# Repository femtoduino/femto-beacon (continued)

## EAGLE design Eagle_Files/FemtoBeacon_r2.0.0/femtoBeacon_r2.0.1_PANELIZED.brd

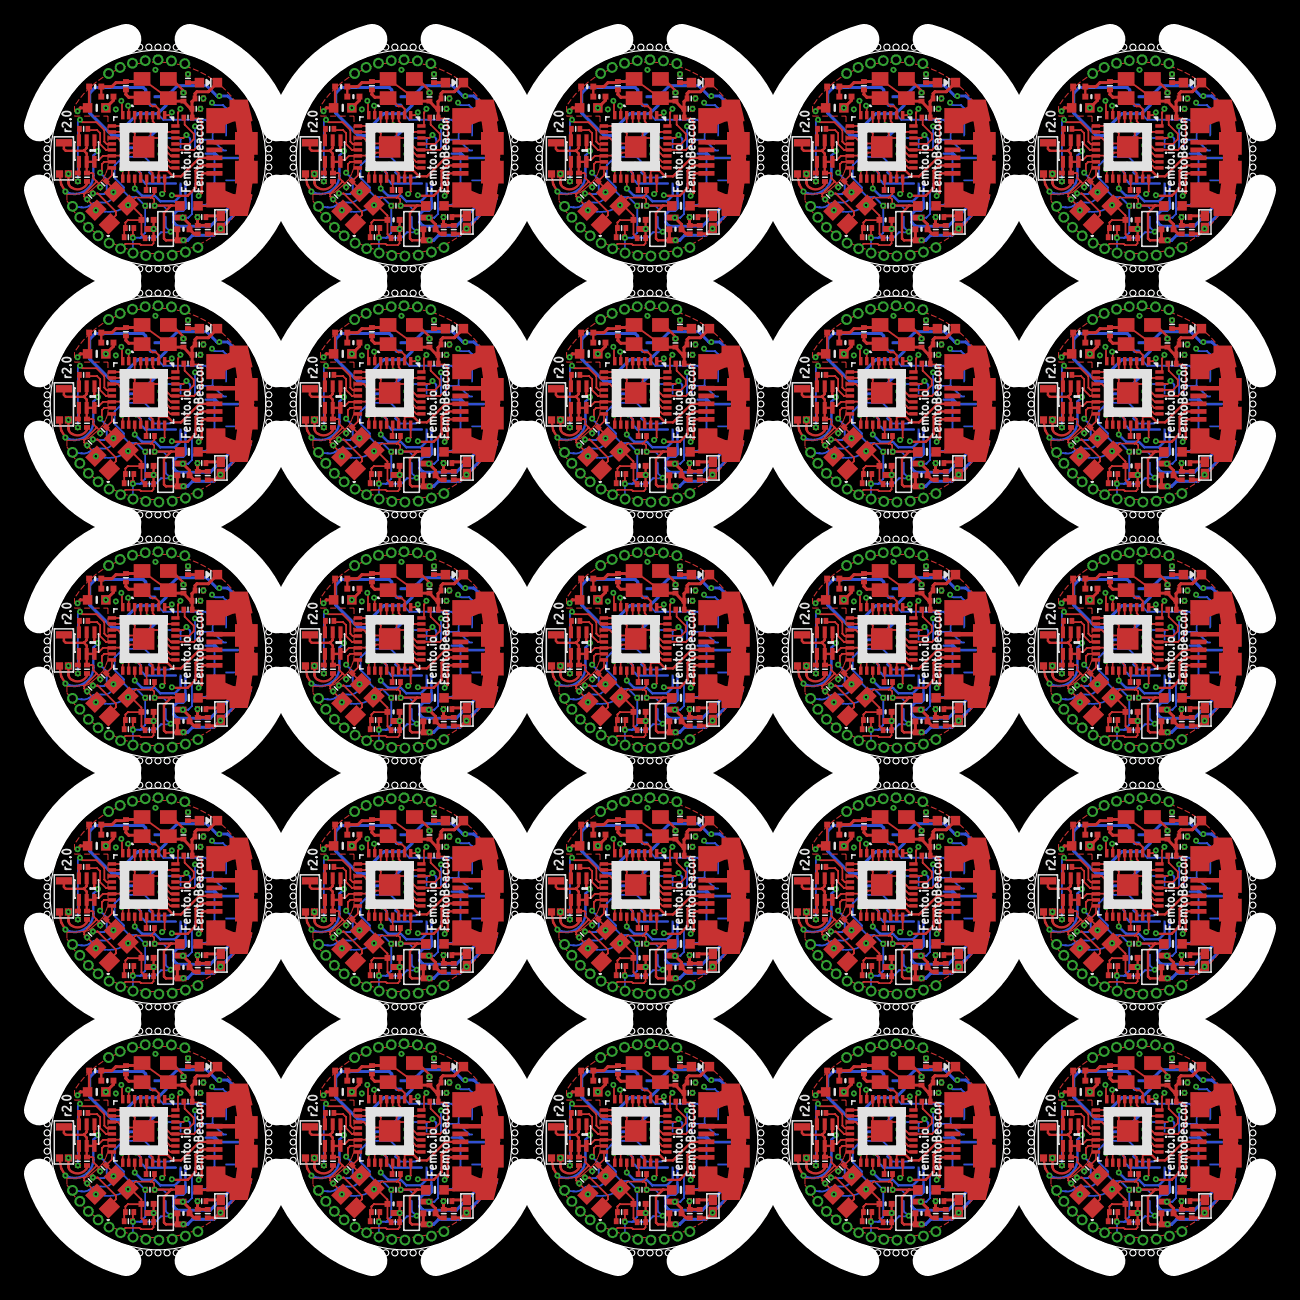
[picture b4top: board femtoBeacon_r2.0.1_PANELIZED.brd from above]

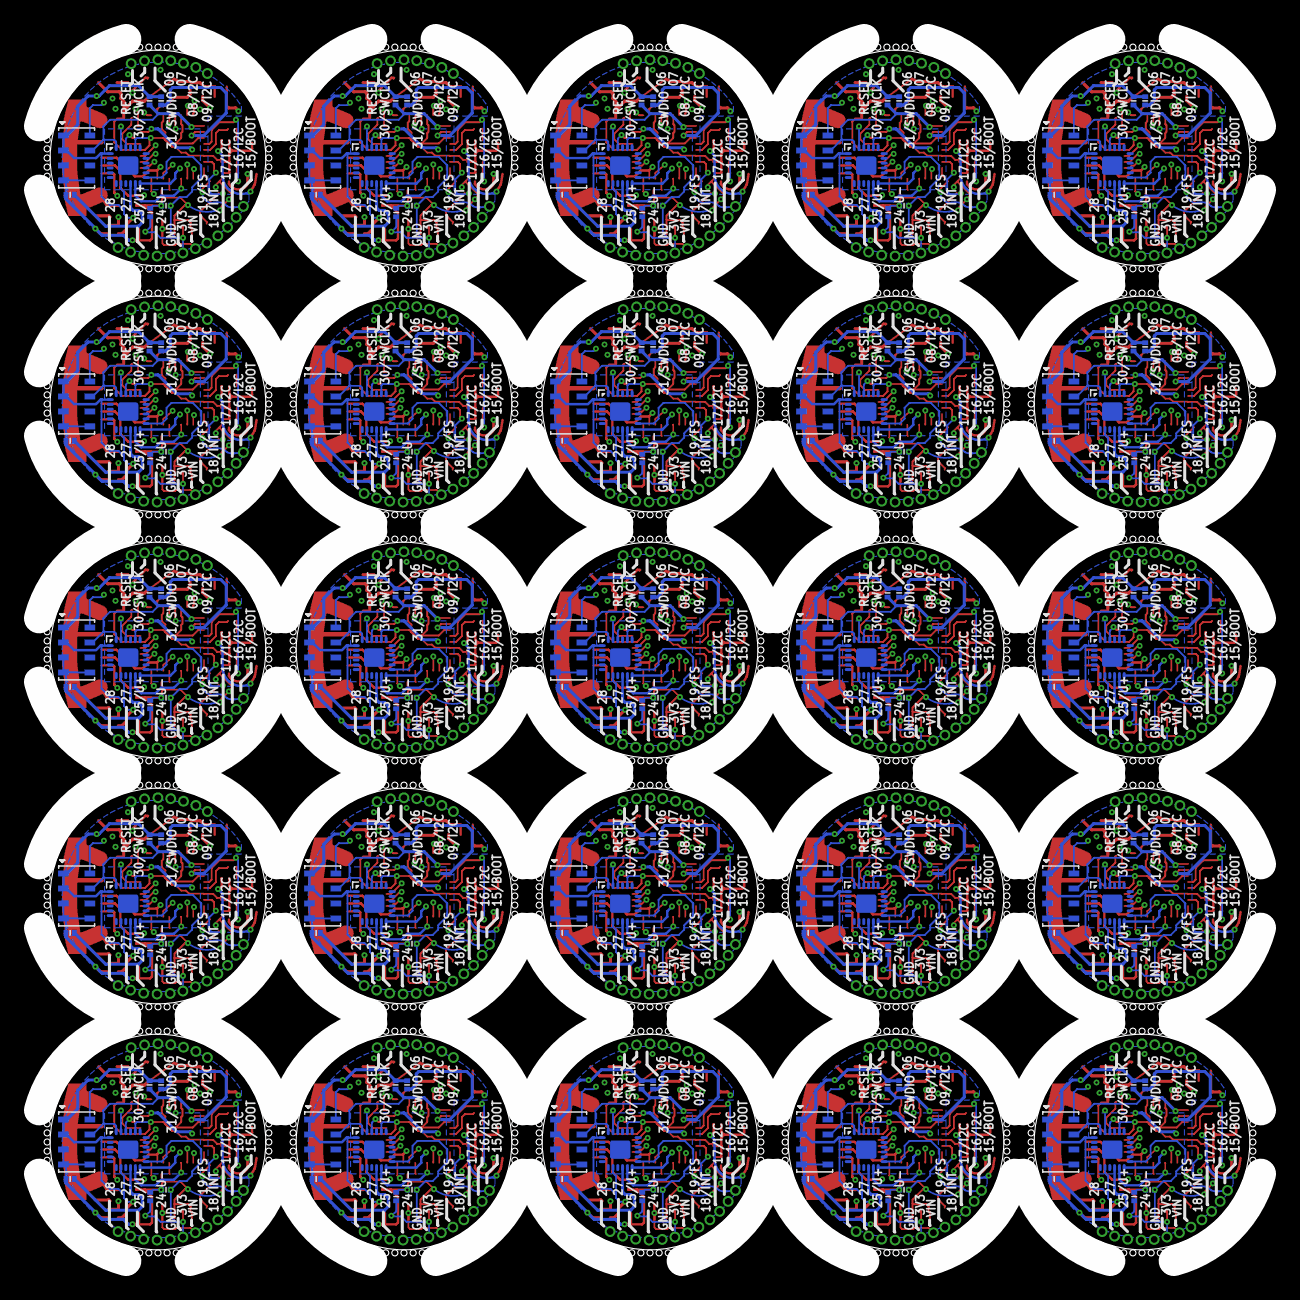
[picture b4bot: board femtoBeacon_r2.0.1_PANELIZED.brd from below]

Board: 4 copper layers, 102.0 x 102.0 mm, 1500 parts (175 on the bottom side), 900 nets.

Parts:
ANT, ANT1, ANT2, ANT3, ANT4, ANT5, ANT6, ANT7, ANT8, ANT9, ANT10, ANT11, ANT12, ANT13, ANT14, ANT15, ANT16, ANT17, ANT18, ANT19, ANT20, ANT21, ANT22, ANT23, ANT24: PULSE_ANT_2.4GHZ; ANT_BAR
BAL, BAL1, BAL2, BAL3, BAL4, BAL5, BAL6, BAL7, BAL8, BAL9, BAL10, BAL11, BAL12, BAL13, BAL14, BAL15, BAL16, BAL17, BAL18, BAL19, BAL20, BAL21, BAL22, BAL23, BAL24: JOHANSON_2450BM15A0015E; 0805_BALUN
BARO, BARO1, BARO2, BARO3, BARO4, BARO5, BARO6, BARO7, BARO8, BARO9, BARO10, BARO11, BARO12, BARO13, BARO14, BARO15, BARO16, BARO17, BARO18, BARO19, BARO20, BARO21, BARO22, BARO23, BARO24: MS5611-01BA03
BTN, BTN1, BTN2, BTN3, BTN4, BTN5, BTN6, BTN7, BTN8, BTN9, BTN10, BTN11, BTN12, BTN13, BTN14, BTN15, BTN16, BTN17, BTN18, BTN19, BTN20, BTN21, BTN22, BTN23, BTN24: DNP; SPST_SMD
C1, C2, C8, C9, C10, C16, C17, C18, C19, C25, C26, C27, C28, C29, C30, C32, C33, C36, C45, C46, C47, C48, C52, C53, C54, C55, C56, C59, C68, C69, C70, C71, C75, C76, C77, C78, C79, C82, C91, C92, C93, C94, C98, C99, C100, C101, C102, C105, C114, C115, C116, C117, C121, C122, C123, C124, C125, C128, C137, C138, C139, C140, C144, C145, C146, C147, C148, C151, C160, C161, C162, C163, C167, C168, C169, C170, C171, C174, C183, C184, C185, C186, C190, C191, C192, C193, C194, C197, C206, C207, C208, C209, C213, C214, C215, C216, C217, C220, C229, C230, C231, C232, C236, C237, C238, C239, C240, C243, C252, C253, C254, C255, C259, C260, C261, C262, C263, C266, C275, C276, C277, C278, C282, C283, C284, C285, C286, C289, C298, C299, C300, C301, C305, C306, C307, C308, C309, C312, C321, C322, C323, C324, C328, C329, C330, C331, C332, C335, C344, C345, C346, C347, C351, C352, C353, C354, C355, C358, C367, C368, C369, C370, C374, C375, C376, C377, C378, C381, C390, C391, C392, C393, C397, C398, C399, C400, C401, C404, C413, C414, C415, C416, C420, C421, C422, C423, C424, C427, C436, C437, C438, C439, C443, C444, C445, C446, C447, C450, C459, C460, C461, C462, C466, C467, C468, C469, C470, C473, C482, C483, C484, C485, C489, C490, C491, C492, C493, C496, C505, C506, C507, C508, C512, C513, C514, C515, C516, C519, C528, C529, C530, C531, C535, C536, C537, C538, C539, C542, C551, C552, C553, C554, C558, C559, C560, C561, C562, C565, C574, C575: 0.1uF; PART
C3, C4, C37, C38, C60, C61, C83, C84, C106, C107, C129, C130, C152, C153, C175, C176, C198, C199, C221, C222, C244, C245, C267, C268, C290, C291, C313, C314, C336, C337, C359, C360, C382, C383, C405, C406, C428, C429, C451, C452, C474, C475, C497, C498, C520, C521, C543, C544, C566, C567: 10pF; PART
C5, C6, C20, C23, C49, C50, C72, C73, C95, C96, C118, C119, C141, C142, C164, C165, C187, C188, C210, C211, C233, C234, C256, C257, C279, C280, C302, C303, C325, C326, C348, C349, C371, C372, C394, C395, C417, C418, C440, C441, C463, C464, C486, C487, C509, C510, C532, C533, C555, C556: 2.2uF; _0402MP
C7, C24, C51, C74, C97, C120, C143, C166, C189, C212, C235, C258, C281, C304, C327, C350, C373, C396, C419, C442, C465, C488, C511, C534, C557: 0.47uF; PART
C11, C12, C39, C40, C62, C63, C85, C86, C108, C109, C131, C132, C154, C155, C177, C178, C200, C201, C223, C224, C246, C247, C269, C270, C292, C293, C315, C316, C338, C339, C361, C362, C384, C385, C407, C408, C430, C431, C453, C454, C476, C477, C499, C500, C522, C523, C545, C546, C568, C569: 22pF, C0G, 5%; PART
C13, C41, C64, C87, C110, C133, C156, C179, C202, C225, C248, C271, C294, C317, C340, C363, C386, C409, C432, C455, C478, C501, C524, C547, C570: DNP; PART
C14, C15, C42, C43, C65, C66, C88, C89, C111, C112, C134, C135, C157, C158, C180, C181, C203, C204, C226, C227, C249, C250, C272, C273, C295, C296, C318, C319, C341, C342, C364, C365, C387, C388, C410, C411, C433, C434, C456, C457, C479, C480, C502, C503, C525, C526, C548, C549, C571, C572: 9pF; PART
C21, C22, C34, C35, C57, C58, C80, C81, C103, C104, C126, C127, C149, C150, C172, C173, C195, C196, C218, C219, C241, C242, C264, C265, C287, C288, C310, C311, C333, C334, C356, C357, C379, C380, C402, C403, C425, C426, C448, C449, C471, C472, C494, C495, C517, C518, C540, C541, C563, C564: 10uF; _0402MP
C31, C44, C67, C90, C113, C136, C159, C182, C205, C228, C251, C274, C297, C320, C343, C366, C389, C412, C435, C458, C481, C504, C527, C550, C573: 10nF; PART
FB1, FB2, FB3, FB4, FB5, FB6, FB7, FB8, FB9, FB10, FB11, FB12, FB13, FB14, FB15, FB16, FB17, FB18, FB19, FB20, FB21, FB22, FB23, FB24, FB25: _0603MP
IC, IC1, IC2, IC3, IC4, IC5, IC6, IC7, IC8, IC9, IC10, IC11, IC12, IC13, IC14, IC15, IC16, IC17, IC18, IC19, IC20, IC21, IC22, IC23, IC24: ATSAMR21E18A-MUT; QFN32
IMU, IMU1, IMU2, IMU3, IMU4, IMU5, IMU6, IMU7, IMU8, IMU9, IMU10, IMU11, IMU12, IMU13, IMU14, IMU15, IMU16, IMU17, IMU18, IMU19, IMU20, IMU21, IMU22, IMU23, IMU24: MPU-9250; QFN_3X3MM
L1, L2, L3, L4, L5, L6, L7, L8, L9, L10, L11, L12, L13, L14, L15, L16, L17, L18, L19, L20, L21, L22, L23, L24, L25: 10uH; _0603MP
LDO_VREG, LDO_VREG1, LDO_VREG2, LDO_VREG3, LDO_VREG4, LDO_VREG5, LDO_VREG6, LDO_VREG7, LDO_VREG8, LDO_VREG9, LDO_VREG10, LDO_VREG11, LDO_VREG12, LDO_VREG13, LDO_VREG14, LDO_VREG15, LDO_VREG16, LDO_VREG17, LDO_VREG18, LDO_VREG19, LDO_VREG20, LDO_VREG21, LDO_VREG22, LDO_VREG23, LDO_VREG24: MCP1700T-3302E/TT
LED, LED1, LED2, LED3, LED4, LED5, LED6, LED7, LED8, LED9, LED10, LED11, LED12, LED13, LED14, LED15, LED16, LED17, LED18, LED19, LED20, LED21, LED22, LED23, LED24: BLUE; CHIPLED_0603_NOOUTLINE
R1, R3, R4, R6, R11, R13, R16, R18, R21, R23, R26, R28, R31, R33, R36, R38, R41, R43, R46, R48, R51, R53, R56, R58, R61, R63, R66, R68, R71, R73, R76, R78, R81, R83, R86, R88, R91, R93, R96, R98, R101, R103, R106, R108, R111, R113, R116, R118, R121, R123: 330; PART
R2, R5, R12, R17, R22, R27, R32, R37, R42, R47, R52, R57, R62, R67, R72, R77, R82, R87, R92, R97, R102, R107, R112, R117, R122: 10K; PART
R7, R8, R9, R10, R14, R15, R19, R20, R24, R25, R29, R30, R34, R35, R39, R40, R44, R45, R49, R50, R54, R55, R59, R60, R64, R65, R69, R70, R74, R75, R79, R80, R84, R85, R89, R90, R94, R95, R99, R100, R104, R105, R109, R110, R114, R115, R119, R120, R124, R125: 2.2K; PART
U$1, U$2, U$3, U$4, U$5, U$6, U$7, U$8, U$9, U$10, U$11, U$12, U$13, U$14, U$15, U$16, U$17, U$18, U$19, U$20, U$21, U$22, U$23, U$24, U$25, U$26, U$27, U$28, U$29, U$30, U$31, U$32, U$33, U$34, U$35, U$36, U$37, U$38, U$39, U$40, U$41, U$42, U$43, U$44, U$45, U$46, U$47, U$48, U$49, U$50, U$51, U$52, U$53, U$54, U$55, U$56, U$57, U$58, U$59, U$60, U$61, U$62, U$63, U$64, U$65, U$66, U$67, U$68, U$69, U$70, U$71, U$72, U$73, U$74, U$75, U$76, U$77, U$78, U$79, U$80, U$81, U$82, U$83, U$84, U$85, U$86, U$87, U$88, U$89, U$90, U$91, U$92, U$93, U$94, U$95, U$96, U$97, U$98, U$99, U$100, U$101, U$102, U$103, U$104, U$105, U$106, U$107, U$108, U$109, U$110, U$111, U$112, U$113, U$114, U$115, U$116, U$117, U$118, U$119, U$120, U$121, U$122, U$123, U$124, U$125, U$126, U$127, U$128, U$129, U$130, U$131, U$132, U$133, U$134, U$135, U$136, U$137, U$138, U$139, U$140, U$141, U$142, U$143, U$144, U$145, U$146, U$147, U$148, U$149, U$150, U$151, U$152, U$153, U$154, U$155, U$156, U$157, U$158, U$159, U$160, U$161, U$162, U$163, U$164, U$165, U$166, U$167, U$168, U$169, U$170, U$171, U$172, U$173, U$174, U$175, U$176, U$177, U$178, U$179, U$180, U$181, U$182, U$183, U$184, U$185, U$186, U$187, U$188, U$189, U$190, U$191, U$192, U$193, U$194, U$195, U$196, U$197, U$198, U$199, U$200, U$201, U$202, U$203, U$204, U$205, U$206, U$207, U$208, U$209, U$210, U$211, U$212, U$213, U$214, U$215, U$216, U$217, U$218, U$219, U$220, U$221, U$222, U$223, U$224, U$225, U$226, U$227, U$228, U$229, U$230, U$231, U$232, U$233, U$234, U$235, U$236, U$237, U$238, U$239, U$240, U$241, U$242, U$243, U$244, U$245, U$246, U$247, U$248, U$249, U$250, U$251, U$252, U$253, U$254, U$255, U$256, U$257, U$258, U$259, U$260, U$261, U$262, U$263, U$264, U$265, U$266, U$267, U$268, U$269, U$270, U$271, U$272, U$273, U$274, U$275, U$276, U$277, U$278, U$279, U$280, U$281, U$282, U$283, U$284, U$285, U$286, U$287, U$288, U$289, U$290, U$291, U$292, U$293, U$294, U$295, U$296, U$297, U$298, U$299, U$300, U$301, U$302, U$303, U$304, U$305, U$306, U$307, U$308, U$309, U$310, U$311, U$312, U$313, U$314, U$315, U$316, U$317, U$318, U$319, U$320, U$321, U$322, U$323, U$324, U$325, U$326, U$327, U$328, U$329, U$330, U$331, U$332, U$333, U$334, U$335, U$336, U$337, U$338, U$339, U$340, U$341, U$342, U$343, U$344, U$345, U$346, U$347, U$348, U$349, U$350, U$351, U$352, U$353, U$354, U$355, U$356, U$357, U$358, U$359, U$360, U$361, U$362, U$363, U$364, U$365, U$366, U$367, U$368, U$369, U$370, U$371, U$372, U$373, U$374, U$375, U$376, U$377, U$378, U$379, U$380, U$381, U$382, U$383, U$384, U$385, U$386, U$387, U$388, U$389, U$390, U$391, U$392, U$393, U$394, U$395, U$396, U$397, U$398, U$399, U$400, U$401, U$402, U$403, U$404, U$405, U$406, U$407, U$408, U$409, U$410, U$411, U$412, U$413, U$414, U$415, U$416, U$417, U$418, U$419, U$420, U$421, U$422, U$423, U$424, U$425, U$426, U$427, U$428, U$429, U$430, U$431, U$432, U$433, U$434, U$435, U$436, U$437, U$438, U$439, U$440, U$441, U$442, U$443, U$444, U$445, U$446, U$447, U$448, U$449, U$450, U$451, U$452, U$453, U$454, U$455, U$456, U$457, U$458, U$459, U$460, U$461, U$462, U$463, U$464, U$465, U$466, U$467, U$468, U$469, U$470, U$471, U$472, U$473, U$474, U$475: 1X1_ROUND
USB, USB1, USB2, USB3, USB4, USB5, USB6, USB7, USB8, USB9, USB10, USB11, USB12, USB13, USB14, USB15, USB16, USB17, USB18, USB19, USB20, USB21, USB22, USB23, USB24: USB_MICROB; USB_MICROB_PACKAGE
XOSC, XOSC1, XOSC2, XOSC3, XOSC4, XOSC5, XOSC6, XOSC7, XOSC8, XOSC9, XOSC10, XOSC11, XOSC12, XOSC13, XOSC14, XOSC15, XOSC16, XOSC17, XOSC18, XOSC19, XOSC20, XOSC21, XOSC22, XOSC23, XOSC24: 12MHz; TSX-3225
XOSCRF, XOSCRF1, XOSCRF2, XOSCRF3, XOSCRF4, XOSCRF5, XOSCRF6, XOSCRF7, XOSCRF8, XOSCRF9, XOSCRF10, XOSCRF11, XOSCRF12, XOSCRF13, XOSCRF14, XOSCRF15, XOSCRF16, XOSCRF17, XOSCRF18, XOSCRF19, XOSCRF20, XOSCRF21, XOSCRF22, XOSCRF23, XOSCRF24: 16MHz; TSX-3225

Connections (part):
3.3V: BARO.1, BARO.2, C5.1, C10.1, C16.1, C21.2, C29.1, C30.2, C31.2, IC.24, IC.30, IMU.P$1, IMU.P$8, IMU.P$13, IMU.P$22, L6.1, LDO_VREG.VOUT, R2.2, R8.2, R9.2, U$5.P$1
3.3V1: BARO1.1, BARO1.2, C20.1, C25.1, C28.1, C34.2, C36.1, C44.2, C45.2, IC1.24, IC1.30, IMU1.P$1, IMU1.P$8, IMU1.P$13, IMU1.P$22, L1.1, LDO_VREG1.VOUT, R5.2, R7.2, R10.2, U$6.P$1
3.3V2: BARO2.1, BARO2.2, C49.1, C52.1, C55.1, C57.2, C59.1, C67.2, C68.2, IC2.24, IC2.30, IMU2.P$1, IMU2.P$8, IMU2.P$13, IMU2.P$22, L2.1, LDO_VREG2.VOUT, R12.2, R14.2, R15.2, U$28.P$1
3.3V3: BARO3.1, BARO3.2, C72.1, C75.1, C78.1, C80.2, C82.1, C90.2, C91.2, IC3.24, IC3.30, IMU3.P$1, IMU3.P$8, IMU3.P$13, IMU3.P$22, L3.1, LDO_VREG3.VOUT, R17.2, R19.2, R20.2, U$60.P$1
3.3V4: BARO4.1, BARO4.2, C95.1, C98.1, C101.1, C103.2, C105.1, C113.2, C114.2, IC4.24, IC4.30, IMU4.P$1, IMU4.P$8, IMU4.P$13, IMU4.P$22, L4.1, LDO_VREG4.VOUT, R22.2, R24.2, R25.2, U$79.P$1
3.3V5: BARO5.1, BARO5.2, C118.1, C121.1, C124.1, C126.2, C128.1, C136.2, C137.2, IC5.24, IC5.30, IMU5.P$1, IMU5.P$8, IMU5.P$13, IMU5.P$22, L5.1, LDO_VREG5.VOUT, R27.2, R29.2, R30.2, U$98.P$1
3.3V6: BARO6.1, BARO6.2, C141.1, C144.1, C147.1, C149.2, C151.1, C159.2, C160.2, IC6.24, IC6.30, IMU6.P$1, IMU6.P$8, IMU6.P$13, IMU6.P$22, L7.1, LDO_VREG6.VOUT, R32.2, R34.2, R35.2, U$117.P$1
3.3V7: BARO7.1, BARO7.2, C164.1, C167.1, C170.1, C172.2, C174.1, C182.2, C183.2, IC7.24, IC7.30, IMU7.P$1, IMU7.P$8, IMU7.P$13, IMU7.P$22, L8.1, LDO_VREG7.VOUT, R37.2, R39.2, R40.2, U$136.P$1
3.3V8: BARO8.1, BARO8.2, C187.1, C190.1, C193.1, C195.2, C197.1, C205.2, C206.2, IC8.24, IC8.30, IMU8.P$1, IMU8.P$8, IMU8.P$13, IMU8.P$22, L9.1, LDO_VREG8.VOUT, R42.2, R44.2, R45.2, U$155.P$1
3.3V9: BARO9.1, BARO9.2, C210.1, C213.1, C216.1, C218.2, C220.1, C228.2, C229.2, IC9.24, IC9.30, IMU9.P$1, IMU9.P$8, IMU9.P$13, IMU9.P$22, L10.1, LDO_VREG9.VOUT, R47.2, R49.2, R50.2, U$174.P$1
3.3V10: BARO10.1, BARO10.2, C233.1, C236.1, C239.1, C241.2, C243.1, C251.2, C252.2, IC10.24, IC10.30, IMU10.P$1, IMU10.P$8, IMU10.P$13, IMU10.P$22, L11.1, LDO_VREG10.VOUT, R52.2, R54.2, R55.2, U$193.P$1
3.3V11: BARO11.1, BARO11.2, C256.1, C259.1, C262.1, C264.2, C266.1, C274.2, C275.2, IC11.24, IC11.30, IMU11.P$1, IMU11.P$8, IMU11.P$13, IMU11.P$22, L12.1, LDO_VREG11.VOUT, R57.2, R59.2, R60.2, U$212.P$1
3.3V12: BARO12.1, BARO12.2, C279.1, C282.1, C285.1, C287.2, C289.1, C297.2, C298.2, IC12.24, IC12.30, IMU12.P$1, IMU12.P$8, IMU12.P$13, IMU12.P$22, L13.1, LDO_VREG12.VOUT, R62.2, R64.2, R65.2, U$231.P$1
3.3V13: BARO13.1, BARO13.2, C302.1, C305.1, C308.1, C310.2, C312.1, C320.2, C321.2, IC13.24, IC13.30, IMU13.P$1, IMU13.P$8, IMU13.P$13, IMU13.P$22, L14.1, LDO_VREG13.VOUT, R67.2, R69.2, R70.2, U$250.P$1
3.3V14: BARO14.1, BARO14.2, C325.1, C328.1, C331.1, C333.2, C335.1, C343.2, C344.2, IC14.24, IC14.30, IMU14.P$1, IMU14.P$8, IMU14.P$13, IMU14.P$22, L15.1, LDO_VREG14.VOUT, R72.2, R74.2, R75.2, U$269.P$1
3.3V15: BARO15.1, BARO15.2, C348.1, C351.1, C354.1, C356.2, C358.1, C366.2, C367.2, IC15.24, IC15.30, IMU15.P$1, IMU15.P$8, IMU15.P$13, IMU15.P$22, L16.1, LDO_VREG15.VOUT, R77.2, R79.2, R80.2, U$288.P$1
3.3V16: BARO16.1, BARO16.2, C371.1, C374.1, C377.1, C379.2, C381.1, C389.2, C390.2, IC16.24, IC16.30, IMU16.P$1, IMU16.P$8, IMU16.P$13, IMU16.P$22, L17.1, LDO_VREG16.VOUT, R82.2, R84.2, R85.2, U$307.P$1
3.3V17: BARO17.1, BARO17.2, C394.1, C397.1, C400.1, C402.2, C404.1, C412.2, C413.2, IC17.24, IC17.30, IMU17.P$1, IMU17.P$8, IMU17.P$13, IMU17.P$22, L18.1, LDO_VREG17.VOUT, R87.2, R89.2, R90.2, U$326.P$1
3.3V18: BARO18.1, BARO18.2, C417.1, C420.1, C423.1, C425.2, C427.1, C435.2, C436.2, IC18.24, IC18.30, IMU18.P$1, IMU18.P$8, IMU18.P$13, IMU18.P$22, L19.1, LDO_VREG18.VOUT, R92.2, R94.2, R95.2, U$345.P$1
3.3V19: BARO19.1, BARO19.2, C440.1, C443.1, C446.1, C448.2, C450.1, C458.2, C459.2, IC19.24, IC19.30, IMU19.P$1, IMU19.P$8, IMU19.P$13, IMU19.P$22, L20.1, LDO_VREG19.VOUT, R97.2, R99.2, R100.2, U$364.P$1
3.3V20: BARO20.1, BARO20.2, C463.1, C466.1, C469.1, C471.2, C473.1, C481.2, C482.2, IC20.24, IC20.30, IMU20.P$1, IMU20.P$8, IMU20.P$13, IMU20.P$22, L21.1, LDO_VREG20.VOUT, R102.2, R104.2, R105.2, U$383.P$1
3.3V21: BARO21.1, BARO21.2, C486.1, C489.1, C492.1, C494.2, C496.1, C504.2, C505.2, IC21.24, IC21.30, IMU21.P$1, IMU21.P$8, IMU21.P$13, IMU21.P$22, L22.1, LDO_VREG21.VOUT, R107.2, R109.2, R110.2, U$402.P$1
3.3V22: BARO22.1, BARO22.2, C509.1, C512.1, C515.1, C517.2, C519.1, C527.2, C528.2, IC22.24, IC22.30, IMU22.P$1, IMU22.P$8, IMU22.P$13, IMU22.P$22, L23.1, LDO_VREG22.VOUT, R112.2, R114.2, R115.2, U$421.P$1
3.3V23: BARO23.1, BARO23.2, C532.1, C535.1, C538.1, C540.2, C542.1, C550.2, C551.2, IC23.24, IC23.30, IMU23.P$1, IMU23.P$8, IMU23.P$13, IMU23.P$22, L24.1, LDO_VREG23.VOUT, R117.2, R119.2, R120.2, U$440.P$1
3.3V24: BARO24.1, BARO24.2, C555.1, C558.1, C561.1, C563.2, C565.1, C573.2, C574.2, IC24.24, IC24.30, IMU24.P$1, IMU24.P$8, IMU24.P$13, IMU24.P$22, L25.1, LDO_VREG24.VOUT, R122.2, R124.2, R125.2, U$459.P$1
ANT_OUT: ANT.1, BAL.1
ANT_OUT1: ANT1.1, BAL1.1
ANT_OUT2: ANT2.1, BAL2.1
ANT_OUT3: ANT3.1, BAL3.1
ANT_OUT4: ANT4.1, BAL4.1
ANT_OUT5: ANT5.1, BAL5.1
ANT_OUT6: ANT6.1, BAL6.1
ANT_OUT7: ANT7.1, BAL7.1
ANT_OUT8: ANT8.1, BAL8.1
ANT_OUT9: ANT9.1, BAL9.1
ANT_OUT10: ANT10.1, BAL10.1
ANT_OUT11: ANT11.1, BAL11.1
ANT_OUT12: ANT12.1, BAL12.1
ANT_OUT13: ANT13.1, BAL13.1
ANT_OUT14: ANT14.1, BAL14.1
ANT_OUT15: ANT15.1, BAL15.1
ANT_OUT16: ANT16.1, BAL16.1
ANT_OUT17: ANT17.1, BAL17.1
ANT_OUT18: ANT18.1, BAL18.1
ANT_OUT19: ANT19.1, BAL19.1
ANT_OUT20: ANT20.1, BAL20.1
ANT_OUT21: ANT21.1, BAL21.1
ANT_OUT22: ANT22.1, BAL22.1
ANT_OUT23: ANT23.1, BAL23.1
ANT_OUT24: ANT24.1, BAL24.1
AVDD: C17.1, IC.5
AVDD1: C33.1, IC1.5
AVDD2: C56.1, IC2.5
AVDD3: C79.1, IC3.5
AVDD4: C102.1, IC4.5
AVDD5: C125.1, IC5.5
AVDD6: C148.1, IC6.5
AVDD7: C171.1, IC7.5
AVDD8: C194.1, IC8.5
AVDD9: C217.1, IC9.5
AVDD10: C240.1, IC10.5
AVDD11: C263.1, IC11.5
AVDD12: C286.1, IC12.5
AVDD13: C309.1, IC13.5
AVDD14: C332.1, IC14.5
AVDD15: C355.1, IC15.5
AVDD16: C378.1, IC16.5
AVDD17: C401.1, IC17.5
AVDD18: C424.1, IC18.5
AVDD19: C447.1, IC19.5
AVDD20: C470.1, IC20.5
AVDD21: C493.1, IC21.5
AVDD22: C516.1, IC22.5
AVDD23: C539.1, IC23.5
AVDD24: C562.1, IC24.5
DVDD: C2.1, IC.21
DVDD1: C19.1, IC1.21
DVDD2: C48.1, IC2.21
DVDD3: C71.1, IC3.21
DVDD4: C94.1, IC4.21
DVDD5: C117.1, IC5.21
DVDD6: C140.1, IC6.21
DVDD7: C163.1, IC7.21
DVDD8: C186.1, IC8.21
DVDD9: C209.1, IC9.21
DVDD10: C232.1, IC10.21
DVDD11: C255.1, IC11.21
DVDD12: C278.1, IC12.21
DVDD13: C301.1, IC13.21
DVDD14: C324.1, IC14.21
DVDD15: C347.1, IC15.21
DVDD16: C370.1, IC16.21
DVDD17: C393.1, IC17.21
DVDD18: C416.1, IC18.21
DVDD19: C439.1, IC19.21
DVDD20: C462.1, IC20.21
DVDD21: C485.1, IC21.21
DVDD22: C508.1, IC22.21
DVDD23: C531.1, IC23.21
DVDD24: C554.1, IC24.21
GND: ANT.3, BAL.2, BAL.5, BAL.6, BARO.3, BARO.4, BARO.5, BTN.2, C1.2, C2.2, C3.1, C4.2, C5.2, C6.2, C7.2, C8.2, C9.2, C10.2, C13.2, C14.1, C15.2, C16.2, C17.2, C21.1, C22.1, C29.2, C30.1, C31.1, C32.2, FB1.2, IC.3, IC.6, IC.11, IC.14, IC.28, IC.33, IMU.P$20, LDO_VREG.GND, LED.C, U$2.P$1, XOSC.2, XOSC.4, XOSCRF.2, XOSCRF.4
GND1: ANT1.3, BAL1.2, BAL1.5, BAL1.6, BARO1.3, BARO1.4, BARO1.5, BTN1.2, C18.2, C19.2, C20.2, C23.2, C24.2, C25.2, C26.2, C27.2, C28.2, C33.2, C34.1, C35.1, C36.2, C37.1, C38.2, C41.2, C42.1, C43.2, C44.1, C45.1, C46.2, FB2.2, IC1.3, IC1.6, IC1.11, IC1.14, IC1.28, IC1.33, IMU1.P$20, LDO_VREG1.GND, LED1.C, U$4.P$1, XOSC1.2, XOSC1.4, XOSCRF1.2, XOSCRF1.4
GND2: ANT2.3, BAL2.2, BAL2.5, BAL2.6, BARO2.3, BARO2.4, BARO2.5, BTN2.2, C47.2, C48.2, C49.2, C50.2, C51.2, C52.2, C53.2, C54.2, C55.2, C56.2, C57.1, C58.1, C59.2, C60.1, C61.2, C64.2, C65.1, C66.2, C67.1, C68.1, C69.2, FB3.2, IC2.3, IC2.6, IC2.11, IC2.14, IC2.28, IC2.33, IMU2.P$20, LDO_VREG2.GND, LED2.C, U$27.P$1, XOSC2.2, XOSC2.4, XOSCRF2.2, XOSCRF2.4
GND3: ANT3.3, BAL3.2, BAL3.5, BAL3.6, BARO3.3, BARO3.4, BARO3.5, BTN3.2, C70.2, C71.2, C72.2, C73.2, C74.2, C75.2, C76.2, C77.2, C78.2, C79.2, C80.1, C81.1, C82.2, C83.1, C84.2, C87.2, C88.1, C89.2, C90.1, C91.1, C92.2, FB4.2, IC3.3, IC3.6, IC3.11, IC3.14, IC3.28, IC3.33, IMU3.P$20, LDO_VREG3.GND, LED3.C, U$59.P$1, XOSC3.2, XOSC3.4, XOSCRF3.2, XOSCRF3.4
GND4: ANT4.3, BAL4.2, BAL4.5, BAL4.6, BARO4.3, BARO4.4, BARO4.5, BTN4.2, C93.2, C94.2, C95.2, C96.2, C97.2, C98.2, C99.2, C100.2, C101.2, C102.2, C103.1, C104.1, C105.2, C106.1, C107.2, C110.2, C111.1, C112.2, C113.1, C114.1, C115.2, FB5.2, IC4.3, IC4.6, IC4.11, IC4.14, IC4.28, IC4.33, IMU4.P$20, LDO_VREG4.GND, LED4.C, U$78.P$1, XOSC4.2, XOSC4.4, XOSCRF4.2, XOSCRF4.4
GND5: ANT5.3, BAL5.2, BAL5.5, BAL5.6, BARO5.3, BARO5.4, BARO5.5, BTN5.2, C116.2, C117.2, C118.2, C119.2, C120.2, C121.2, C122.2, C123.2, C124.2, C125.2, C126.1, C127.1, C128.2, C129.1, C130.2, C133.2, C134.1, C135.2, C136.1, C137.1, C138.2, FB6.2, IC5.3, IC5.6, IC5.11, IC5.14, IC5.28, IC5.33, IMU5.P$20, LDO_VREG5.GND, LED5.C, U$97.P$1, XOSC5.2, XOSC5.4, XOSCRF5.2, XOSCRF5.4
GND6: ANT6.3, BAL6.2, BAL6.5, BAL6.6, BARO6.3, BARO6.4, BARO6.5, BTN6.2, C139.2, C140.2, C141.2, C142.2, C143.2, C144.2, C145.2, C146.2, C147.2, C148.2, C149.1, C150.1, C151.2, C152.1, C153.2, C156.2, C157.1, C158.2, C159.1, C160.1, C161.2, FB7.2, IC6.3, IC6.6, IC6.11, IC6.14, IC6.28, IC6.33, IMU6.P$20, LDO_VREG6.GND, LED6.C, U$116.P$1, XOSC6.2, XOSC6.4, XOSCRF6.2, XOSCRF6.4
GND7: ANT7.3, BAL7.2, BAL7.5, BAL7.6, BARO7.3, BARO7.4, BARO7.5, BTN7.2, C162.2, C163.2, C164.2, C165.2, C166.2, C167.2, C168.2, C169.2, C170.2, C171.2, C172.1, C173.1, C174.2, C175.1, C176.2, C179.2, C180.1, C181.2, C182.1, C183.1, C184.2, FB8.2, IC7.3, IC7.6, IC7.11, IC7.14, IC7.28, IC7.33, IMU7.P$20, LDO_VREG7.GND, LED7.C, U$135.P$1, XOSC7.2, XOSC7.4, XOSCRF7.2, XOSCRF7.4
GND8: ANT8.3, BAL8.2, BAL8.5, BAL8.6, BARO8.3, BARO8.4, BARO8.5, BTN8.2, C185.2, C186.2, C187.2, C188.2, C189.2, C190.2, C191.2, C192.2, C193.2, C194.2, C195.1, C196.1, C197.2, C198.1, C199.2, C202.2, C203.1, C204.2, C205.1, C206.1, C207.2, FB9.2, IC8.3, IC8.6, IC8.11, IC8.14, IC8.28, IC8.33, IMU8.P$20, LDO_VREG8.GND, LED8.C, U$154.P$1, XOSC8.2, XOSC8.4, XOSCRF8.2, XOSCRF8.4
GND9: ANT9.3, BAL9.2, BAL9.5, BAL9.6, BARO9.3, BARO9.4, BARO9.5, BTN9.2, C208.2, C209.2, C210.2, C211.2, C212.2, C213.2, C214.2, C215.2, C216.2, C217.2, C218.1, C219.1, C220.2, C221.1, C222.2, C225.2, C226.1, C227.2, C228.1, C229.1, C230.2, FB10.2, IC9.3, IC9.6, IC9.11, IC9.14, IC9.28, IC9.33, IMU9.P$20, LDO_VREG9.GND, LED9.C, U$173.P$1, XOSC9.2, XOSC9.4, XOSCRF9.2, XOSCRF9.4
GND10: ANT10.3, BAL10.2, BAL10.5, BAL10.6, BARO10.3, BARO10.4, BARO10.5, BTN10.2, C231.2, C232.2, C233.2, C234.2, C235.2, C236.2, C237.2, C238.2, C239.2, C240.2, C241.1, C242.1, C243.2, C244.1, C245.2, C248.2, C249.1, C250.2, C251.1, C252.1, C253.2, FB11.2, IC10.3, IC10.6, IC10.11, IC10.14, IC10.28, IC10.33, IMU10.P$20, LDO_VREG10.GND, LED10.C, U$192.P$1, XOSC10.2, XOSC10.4, XOSCRF10.2, XOSCRF10.4
GND11: ANT11.3, BAL11.2, BAL11.5, BAL11.6, BARO11.3, BARO11.4, BARO11.5, BTN11.2, C254.2, C255.2, C256.2, C257.2, C258.2, C259.2, C260.2, C261.2, C262.2, C263.2, C264.1, C265.1, C266.2, C267.1, C268.2, C271.2, C272.1, C273.2, C274.1, C275.1, C276.2, FB12.2, IC11.3, IC11.6, IC11.11, IC11.14, IC11.28, IC11.33, IMU11.P$20, LDO_VREG11.GND, LED11.C, U$211.P$1, XOSC11.2, XOSC11.4, XOSCRF11.2, XOSCRF11.4
GND12: ANT12.3, BAL12.2, BAL12.5, BAL12.6, BARO12.3, BARO12.4, BARO12.5, BTN12.2, C277.2, C278.2, C279.2, C280.2, C281.2, C282.2, C283.2, C284.2, C285.2, C286.2, C287.1, C288.1, C289.2, C290.1, C291.2, C294.2, C295.1, C296.2, C297.1, C298.1, C299.2, FB13.2, IC12.3, IC12.6, IC12.11, IC12.14, IC12.28, IC12.33, IMU12.P$20, LDO_VREG12.GND, LED12.C, U$230.P$1, XOSC12.2, XOSC12.4, XOSCRF12.2, XOSCRF12.4
GND13: ANT13.3, BAL13.2, BAL13.5, BAL13.6, BARO13.3, BARO13.4, BARO13.5, BTN13.2, C300.2, C301.2, C302.2, C303.2, C304.2, C305.2, C306.2, C307.2, C308.2, C309.2, C310.1, C311.1, C312.2, C313.1, C314.2, C317.2, C318.1, C319.2, C320.1, C321.1, C322.2, FB14.2, IC13.3, IC13.6, IC13.11, IC13.14, IC13.28, IC13.33, IMU13.P$20, LDO_VREG13.GND, LED13.C, U$249.P$1, XOSC13.2, XOSC13.4, XOSCRF13.2, XOSCRF13.4
GND14: ANT14.3, BAL14.2, BAL14.5, BAL14.6, BARO14.3, BARO14.4, BARO14.5, BTN14.2, C323.2, C324.2, C325.2, C326.2, C327.2, C328.2, C329.2, C330.2, C331.2, C332.2, C333.1, C334.1, C335.2, C336.1, C337.2, C340.2, C341.1, C342.2, C343.1, C344.1, C345.2, FB15.2, IC14.3, IC14.6, IC14.11, IC14.14, IC14.28, IC14.33, IMU14.P$20, LDO_VREG14.GND, LED14.C, U$268.P$1, XOSC14.2, XOSC14.4, XOSCRF14.2, XOSCRF14.4
GND15: ANT15.3, BAL15.2, BAL15.5, BAL15.6, BARO15.3, BARO15.4, BARO15.5, BTN15.2, C346.2, C347.2, C348.2, C349.2, C350.2, C351.2, C352.2, C353.2, C354.2, C355.2, C356.1, C357.1, C358.2, C359.1, C360.2, C363.2, C364.1, C365.2, C366.1, C367.1, C368.2, FB16.2, IC15.3, IC15.6, IC15.11, IC15.14, IC15.28, IC15.33, IMU15.P$20, LDO_VREG15.GND, LED15.C, U$287.P$1, XOSC15.2, XOSC15.4, XOSCRF15.2, XOSCRF15.4
GND16: ANT16.3, BAL16.2, BAL16.5, BAL16.6, BARO16.3, BARO16.4, BARO16.5, BTN16.2, C369.2, C370.2, C371.2, C372.2, C373.2, C374.2, C375.2, C376.2, C377.2, C378.2, C379.1, C380.1, C381.2, C382.1, C383.2, C386.2, C387.1, C388.2, C389.1, C390.1, C391.2, FB17.2, IC16.3, IC16.6, IC16.11, IC16.14, IC16.28, IC16.33, IMU16.P$20, LDO_VREG16.GND, LED16.C, U$306.P$1, XOSC16.2, XOSC16.4, XOSCRF16.2, XOSCRF16.4
GND17: ANT17.3, BAL17.2, BAL17.5, BAL17.6, BARO17.3, BARO17.4, BARO17.5, BTN17.2, C392.2, C393.2, C394.2, C395.2, C396.2, C397.2, C398.2, C399.2, C400.2, C401.2, C402.1, C403.1, C404.2, C405.1, C406.2, C409.2, C410.1, C411.2, C412.1, C413.1, C414.2, FB18.2, IC17.3, IC17.6, IC17.11, IC17.14, IC17.28, IC17.33, IMU17.P$20, LDO_VREG17.GND, LED17.C, U$325.P$1, XOSC17.2, XOSC17.4, XOSCRF17.2, XOSCRF17.4
GND18: ANT18.3, BAL18.2, BAL18.5, BAL18.6, BARO18.3, BARO18.4, BARO18.5, BTN18.2, C415.2, C416.2, C417.2, C418.2, C419.2, C420.2, C421.2, C422.2, C423.2, C424.2, C425.1, C426.1, C427.2, C428.1, C429.2, C432.2, C433.1, C434.2, C435.1, C436.1, C437.2, FB19.2, IC18.3, IC18.6, IC18.11, IC18.14, IC18.28, IC18.33, IMU18.P$20, LDO_VREG18.GND, LED18.C, U$344.P$1, XOSC18.2, XOSC18.4, XOSCRF18.2, XOSCRF18.4
GND19: ANT19.3, BAL19.2, BAL19.5, BAL19.6, BARO19.3, BARO19.4, BARO19.5, BTN19.2, C438.2, C439.2, C440.2, C441.2, C442.2, C443.2, C444.2, C445.2, C446.2, C447.2, C448.1, C449.1, C450.2, C451.1, C452.2, C455.2, C456.1, C457.2, C458.1, C459.1, C460.2, FB20.2, IC19.3, IC19.6, IC19.11, IC19.14, IC19.28, IC19.33, IMU19.P$20, LDO_VREG19.GND, LED19.C, U$363.P$1, XOSC19.2, XOSC19.4, XOSCRF19.2, XOSCRF19.4
GND20: ANT20.3, BAL20.2, BAL20.5, BAL20.6, BARO20.3, BARO20.4, BARO20.5, BTN20.2, C461.2, C462.2, C463.2, C464.2, C465.2, C466.2, C467.2, C468.2, C469.2, C470.2, C471.1, C472.1, C473.2, C474.1, C475.2, C478.2, C479.1, C480.2, C481.1, C482.1, C483.2, FB21.2, IC20.3, IC20.6, IC20.11, IC20.14, IC20.28, IC20.33, IMU20.P$20, LDO_VREG20.GND, LED20.C, U$382.P$1, XOSC20.2, XOSC20.4, XOSCRF20.2, XOSCRF20.4
GND21: ANT21.3, BAL21.2, BAL21.5, BAL21.6, BARO21.3, BARO21.4, BARO21.5, BTN21.2, C484.2, C485.2, C486.2, C487.2, C488.2, C489.2, C490.2, C491.2, C492.2, C493.2, C494.1, C495.1, C496.2, C497.1, C498.2, C501.2, C502.1, C503.2, C504.1, C505.1, C506.2, FB22.2, IC21.3, IC21.6, IC21.11, IC21.14, IC21.28, IC21.33, IMU21.P$20, LDO_VREG21.GND, LED21.C, U$401.P$1, XOSC21.2, XOSC21.4, XOSCRF21.2, XOSCRF21.4
GND22: ANT22.3, BAL22.2, BAL22.5, BAL22.6, BARO22.3, BARO22.4, BARO22.5, BTN22.2, C507.2, C508.2, C509.2, C510.2, C511.2, C512.2, C513.2, C514.2, C515.2, C516.2, C517.1, C518.1, C519.2, C520.1, C521.2, C524.2, C525.1, C526.2, C527.1, C528.1, C529.2, FB23.2, IC22.3, IC22.6, IC22.11, IC22.14, IC22.28, IC22.33, IMU22.P$20, LDO_VREG22.GND, LED22.C, U$420.P$1, XOSC22.2, XOSC22.4, XOSCRF22.2, XOSCRF22.4
GND23: ANT23.3, BAL23.2, BAL23.5, BAL23.6, BARO23.3, BARO23.4, BARO23.5, BTN23.2, C530.2, C531.2, C532.2, C533.2, C534.2, C535.2, C536.2, C537.2, C538.2, C539.2, C540.1, C541.1, C542.2, C543.1, C544.2, C547.2, C548.1, C549.2, C550.1, C551.1, C552.2, FB24.2, IC23.3, IC23.6, IC23.11, IC23.14, IC23.28, IC23.33, IMU23.P$20, LDO_VREG23.GND, LED23.C, U$439.P$1, XOSC23.2, XOSC23.4, XOSCRF23.2, XOSCRF23.4
GND24: ANT24.3, BAL24.2, BAL24.5, BAL24.6, BARO24.3, BARO24.4, BARO24.5, BTN24.2, C553.2, C554.2, C555.2, C556.2, C557.2, C558.2, C559.2, C560.2, C561.2, C562.2, C563.1, C564.1, C565.2, C566.1, C567.2, C570.2, C571.1, C572.2, C573.1, C574.1, C575.2, FB25.2, IC24.3, IC24.6, IC24.11, IC24.14, IC24.28, IC24.33, IMU24.P$20, LDO_VREG24.GND, LED24.C, U$458.P$1, XOSC24.2, XOSC24.4, XOSCRF24.2, XOSCRF24.4
unnamed: BAL.3, C11.2
unnamed: ANT.2, C13.1
unnamed: BAL.4, C12.2
unnamed: C32.1, IMU.P$10
unnamed: FB1.1, USB.5, USB.6, USB.7, USB.8, USB.9, USB.10, USB.11
unnamed: BTN1.1, R3.1
unnamed: LED1.A, R6.2
unnamed: BAL1.3, C39.2
unnamed: BAL1.4, C40.2
unnamed: ANT1.2, C41.1
unnamed: C46.1, IMU1.P$10
unnamed: LED.A, R4.2
unnamed: FB2.1, USB1.5, USB1.6, USB1.7, USB1.8, USB1.9, USB1.10, USB1.11
unnamed: BTN2.1, R11.1
unnamed: LED2.A, R13.2
unnamed: BAL2.3, C62.2
unnamed: BAL2.4, C63.2
unnamed: ANT2.2, C64.1
unnamed: C69.1, IMU2.P$10
unnamed: FB3.1, USB2.5, USB2.6, USB2.7, USB2.8, USB2.9, USB2.10, USB2.11
unnamed: BTN3.1, R16.1
unnamed: LED3.A, R18.2
unnamed: BTN.1, R1.1
unnamed: BAL3.3, C85.2
unnamed: BAL3.4, C86.2
unnamed: ANT3.2, C87.1
unnamed: C92.1, IMU3.P$10
unnamed: FB4.1, USB3.5, USB3.6, USB3.7, USB3.8, USB3.9, USB3.10, USB3.11
unnamed: BTN4.1, R21.1
unnamed: LED4.A, R23.2
unnamed: BAL4.3, C108.2
unnamed: BAL4.4, C109.2
unnamed: ANT4.2, C110.1
unnamed: C115.1, IMU4.P$10
unnamed: FB5.1, USB4.5, USB4.6, USB4.7, USB4.8, USB4.9, USB4.10, USB4.11
unnamed: BTN5.1, R26.1
unnamed: LED5.A, R28.2
unnamed: BAL5.3, C131.2
unnamed: BAL5.4, C132.2
unnamed: ANT5.2, C133.1
unnamed: C138.1, IMU5.P$10
unnamed: FB6.1, USB5.5, USB5.6, USB5.7, USB5.8, USB5.9, USB5.10, USB5.11
unnamed: BTN6.1, R31.1
unnamed: LED6.A, R33.2
unnamed: BAL6.3, C154.2
unnamed: BAL6.4, C155.2
unnamed: ANT6.2, C156.1
unnamed: C161.1, IMU6.P$10
unnamed: FB7.1, USB6.5, USB6.6, USB6.7, USB6.8, USB6.9, USB6.10, USB6.11
unnamed: BTN7.1, R36.1
unnamed: LED7.A, R38.2
unnamed: BAL7.3, C177.2
unnamed: BAL7.4, C178.2
unnamed: ANT7.2, C179.1
unnamed: C184.1, IMU7.P$10
unnamed: FB8.1, USB7.5, USB7.6, USB7.7, USB7.8, USB7.9, USB7.10, USB7.11
unnamed: BTN8.1, R41.1
unnamed: LED8.A, R43.2
unnamed: BAL8.3, C200.2
unnamed: BAL8.4, C201.2
unnamed: ANT8.2, C202.1
unnamed: C207.1, IMU8.P$10
unnamed: FB9.1, USB8.5, USB8.6, USB8.7, USB8.8, USB8.9, USB8.10, USB8.11
unnamed: BTN9.1, R46.1
unnamed: LED9.A, R48.2
unnamed: BAL9.3, C223.2
unnamed: BAL9.4, C224.2
unnamed: ANT9.2, C225.1
unnamed: C230.1, IMU9.P$10
unnamed: FB10.1, USB9.5, USB9.6, USB9.7, USB9.8, USB9.9, USB9.10, USB9.11
unnamed: BTN10.1, R51.1
unnamed: LED10.A, R53.2
unnamed: BAL10.3, C246.2
unnamed: BAL10.4, C247.2
unnamed: ANT10.2, C248.1
unnamed: C253.1, IMU10.P$10
unnamed: FB11.1, USB10.5, USB10.6, USB10.7, USB10.8, USB10.9, USB10.10, USB10.11
unnamed: BTN11.1, R56.1
unnamed: LED11.A, R58.2
unnamed: BAL11.3, C269.2
unnamed: BAL11.4, C270.2
unnamed: ANT11.2, C271.1
unnamed: C276.1, IMU11.P$10
unnamed: FB12.1, USB11.5, USB11.6, USB11.7, USB11.8, USB11.9, USB11.10, USB11.11
unnamed: BTN12.1, R61.1
unnamed: LED12.A, R63.2
unnamed: BAL12.3, C292.2
unnamed: BAL12.4, C293.2
unnamed: ANT12.2, C294.1
unnamed: C299.1, IMU12.P$10
unnamed: FB13.1, USB12.5, USB12.6, USB12.7, USB12.8, USB12.9, USB12.10, USB12.11
unnamed: BTN13.1, R66.1
unnamed: LED13.A, R68.2
unnamed: BAL13.3, C315.2
unnamed: BAL13.4, C316.2
unnamed: ANT13.2, C317.1
unnamed: C322.1, IMU13.P$10
unnamed: FB14.1, USB13.5, USB13.6, USB13.7, USB13.8, USB13.9, USB13.10, USB13.11
unnamed: BTN14.1, R71.1
unnamed: LED14.A, R73.2
unnamed: BAL14.3, C338.2
unnamed: BAL14.4, C339.2
unnamed: ANT14.2, C340.1
unnamed: C345.1, IMU14.P$10
unnamed: FB15.1, USB14.5, USB14.6, USB14.7, USB14.8, USB14.9, USB14.10, USB14.11
unnamed: BTN15.1, R76.1
unnamed: LED15.A, R78.2
unnamed: BAL15.3, C361.2
unnamed: BAL15.4, C362.2
unnamed: ANT15.2, C363.1
unnamed: C368.1, IMU15.P$10
unnamed: FB16.1, USB15.5, USB15.6, USB15.7, USB15.8, USB15.9, USB15.10, USB15.11
unnamed: BTN16.1, R81.1
unnamed: LED16.A, R83.2
unnamed: BAL16.3, C384.2
unnamed: BAL16.4, C385.2
unnamed: ANT16.2, C386.1
unnamed: C391.1, IMU16.P$10
unnamed: FB17.1, USB16.5, USB16.6, USB16.7, USB16.8, USB16.9, USB16.10, USB16.11
unnamed: BTN17.1, R86.1
unnamed: LED17.A, R88.2
unnamed: BAL17.3, C407.2
unnamed: BAL17.4, C408.2
unnamed: ANT17.2, C409.1
unnamed: C414.1, IMU17.P$10
unnamed: FB18.1, USB17.5, USB17.6, USB17.7, USB17.8, USB17.9, USB17.10, USB17.11
unnamed: BTN18.1, R91.1
unnamed: LED18.A, R93.2
unnamed: BAL18.3, C430.2
unnamed: BAL18.4, C431.2
unnamed: ANT18.2, C432.1
unnamed: C437.1, IMU18.P$10
unnamed: FB19.1, USB18.5, USB18.6, USB18.7, USB18.8, USB18.9, USB18.10, USB18.11
unnamed: BTN19.1, R96.1
unnamed: LED19.A, R98.2
unnamed: BAL19.3, C453.2
unnamed: BAL19.4, C454.2
unnamed: ANT19.2, C455.1
unnamed: C460.1, IMU19.P$10
unnamed: FB20.1, USB19.5, USB19.6, USB19.7, USB19.8, USB19.9, USB19.10, USB19.11
unnamed: BTN20.1, R101.1
unnamed: LED20.A, R103.2
unnamed: BAL20.3, C476.2
unnamed: BAL20.4, C477.2
unnamed: ANT20.2, C478.1
unnamed: C483.1, IMU20.P$10
unnamed: FB21.1, USB20.5, USB20.6, USB20.7, USB20.8, USB20.9, USB20.10, USB20.11
unnamed: BTN21.1, R106.1
unnamed: LED21.A, R108.2
unnamed: BAL21.3, C499.2
unnamed: BAL21.4, C500.2
unnamed: ANT21.2, C501.1
unnamed: C506.1, IMU21.P$10
unnamed: FB22.1, USB21.5, USB21.6, USB21.7, USB21.8, USB21.9, USB21.10, USB21.11
unnamed: BTN22.1, R111.1
unnamed: LED22.A, R113.2
unnamed: BAL22.3, C522.2
unnamed: BAL22.4, C523.2
unnamed: ANT22.2, C524.1
unnamed: C529.1, IMU22.P$10
unnamed: FB23.1, USB22.5, USB22.6, USB22.7, USB22.8, USB22.9, USB22.10, USB22.11
unnamed: BTN23.1, R116.1
unnamed: LED23.A, R118.2
unnamed: BAL23.3, C545.2
unnamed: BAL23.4, C546.2
unnamed: ANT23.2, C547.1
unnamed: C552.1, IMU23.P$10
unnamed: FB24.1, USB23.5, USB23.6, USB23.7, USB23.8, USB23.9, USB23.10, USB23.11
unnamed: BTN24.1, R121.1
unnamed: LED24.A, R123.2
unnamed: BAL24.3, C568.2
unnamed: BAL24.4, C569.2
unnamed: ANT24.2, C570.1
unnamed: C575.1, IMU24.P$10
unnamed: FB25.1, USB24.5, USB24.6, USB24.7, USB24.8, USB24.9, USB24.10, USB24.11
PA1: IC1.25, U$21.P$1
PA2: IC1.27, U$22.P$1
PA3: IC2.25, U$52.P$1
PA4: IC2.27, U$53.P$1
PA5: IC3.25, U$72.P$1
PA6: IC3.27, U$73.P$1
PA06/A0: IC.7, U$54.P$1
PA06/A1: IC1.7, U$23.P$1
PA06/A2: IC2.7, U$55.P$1
PA06/A3: IC3.7, U$74.P$1
PA06/A4: IC4.7, U$93.P$1
PA06/A5: IC5.7, U$112.P$1
PA06/A6: IC6.7, U$131.P$1
PA06/A7: IC7.7, U$150.P$1
PA06/A8: IC8.7, U$169.P$1
PA06/A9: IC9.7, U$188.P$1
PA06/A10: IC10.7, U$207.P$1
PA06/A11: IC11.7, U$226.P$1
PA06/A12: IC12.7, U$245.P$1
PA06/A13: IC13.7, U$264.P$1
PA06/A14: IC14.7, U$283.P$1
PA06/A15: IC15.7, U$302.P$1
PA06/A16: IC16.7, U$321.P$1
PA06/A17: IC17.7, U$340.P$1
PA06/A18: IC18.7, U$359.P$1
PA06/A19: IC19.7, U$378.P$1
PA06/A20: IC20.7, U$397.P$1
PA06/A21: IC21.7, U$416.P$1
PA06/A22: IC22.7, U$435.P$1
PA06/A23: IC23.7, U$454.P$1
PA06/A24: IC24.7, U$473.P$1
PA7: IC4.25, U$91.P$1
PA07/A1: IC.8, U$43.P$1
PA07/A2: IC1.8, U$17.P$1
PA07/A3: IC2.8, U$44.P$1
PA07/A4: IC3.8, U$68.P$1
PA07/A5: IC4.8, U$87.P$1
PA07/A6: IC5.8, U$106.P$1
PA07/A7: IC6.8, U$125.P$1
PA07/A8: IC7.8, U$144.P$1
PA07/A9: IC8.8, U$163.P$1
PA07/A10: IC9.8, U$182.P$1
PA07/A11: IC10.8, U$201.P$1
PA07/A12: IC11.8, U$220.P$1
PA07/A13: IC12.8, U$239.P$1
PA07/A14: IC13.8, U$258.P$1
PA07/A15: IC14.8, U$277.P$1
PA07/A16: IC15.8, U$296.P$1
PA07/A17: IC16.8, U$315.P$1
PA07/A18: IC17.8, U$334.P$1
PA07/A19: IC18.8, U$353.P$1
PA07/A20: IC19.8, U$372.P$1
PA07/A21: IC20.8, U$391.P$1
PA07/A22: IC21.8, U$410.P$1
PA07/A23: IC22.8, U$429.P$1
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
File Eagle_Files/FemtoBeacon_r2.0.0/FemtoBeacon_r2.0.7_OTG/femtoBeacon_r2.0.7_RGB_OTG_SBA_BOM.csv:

##########################################################################
       Name: Placement Bill of Materials Generator

    Version: 4 (2-sided, top)
         By: Small Batch Assembly
        URL: www.smallbatchassembly.com
 SourceFile: femtoBeacon_r2.0.7_RGB_OTG.brd
   DateTime: 11/24/17 7:52 PM
      Units: inches
##########################################################################
REF,PACKAGE,VALUE,X,Y,ROTATION,
ANT_SMD   , 0479480001            , 0479480001     , 0.2137, 0.5543, 180.0
BALUN   , 0805_BALUN            , JOHANSON_2450BM15A0015E     , 0.3937, 0.5770, 270.0
BTN   , SPST_SMD            , DNP     , 0.8398, 0.3440, 270.0
C1   , PART            , 0.1uF     , 0.7968, 0.3190, 270.0
C2   , PART            , 0.1uF     , 0.6077, 0.4490, 0.0
C5   , _0402MP            , 2.2uF     , 0.7167, 0.3200, 180.0
C6   , _0402MP            , 2.2uF     , 0.5987, 0.3510, 180.0
C7   , PART            , 0.47uF     , 0.6047, 0.2910, 180.0
C8   , PART            , 0.1uF     , 0.7687, 0.7430, 180.0
C9   , PART            , 0.1uF     , 0.7318, 0.6870, 0.0
C10   , PART            , 0.1uF     , 0.5397, 0.3240, 180.0
C11   , _0402MP            , 1.2pF     , 0.3850, 0.4650, 0.0
C12   , PART            , 22pF     , 0.3937, 0.6550, 180.0
C13   , PART            , DNP     , 0.3900, 0.4350, 0.0
C14   , PART            , 9pF     , 0.5277, 0.7920, 270.0
C15   , PART            , 9pF     , 0.7167, 0.7550, 270.0
C16   , PART            , 0.1uF     , 0.6067, 0.3975, 0.0
C17   , PART            , 0.1uF     , 0.7587, 0.7160, 180.0
C21   , _0402MP            , 10uF     , 0.4267, 0.7890, 180.0
C22   , _0402MP            , 10uF     , 0.4667, 0.7560, 0.0
C31   , PART            , 10nF     , 0.5357, 0.2940, 0.0
FB1   , _0603MP            , Ferrite     , 0.7347, 0.3970, 180.0
FID1   , FIDUCIAL_1MM            , FIDUCIAL     , 0.1000, 0.3000, 0.0
FID2   , FIDUCIAL_1MM            , FIDUCIAL     , 0.1000, 0.8000, 0.0
FID3   , FIDUCIAL_1MM            , FIDUCIAL     , 1.2000, 0.8000, 0.0
IC   , QFN32            , ATSAMR21E18A-MUT     , 0.5861, 0.5907, 270.0
L1   , _0603MP            , 1.8nH     , 0.3300, 0.4650, 270.0
L6   , _0603MP            , 10uH     , 0.4317, 0.7190, 0.0
LDO_VREG   , MCP1700T-3302E/TT            , MCP1700T-3302E/TT     , 0.6581, 0.3211, 90.0
R1   , PART            , 330     , 0.7767, 0.3600, 180.0
R2   , PART            , 10K     , 0.7637, 0.3190, 270.0
R4   , PART            , 330     , 0.7760, 0.7880, 0.0
R5   , PART            , 330     , 0.7350, 0.5600, 0.0
R6   , PART            , 330     , 0.7700, 0.8150, 0.0
R7   , PART            , 330     , 0.7800, 0.8450, 0.0
R10   , PART            , 100K     , 0.7750, 0.6140, 90.0
RGBLED   , LRTB_R48G            , LRTB_R48G     , 0.8300, 0.7950, 270.0
USB   , USB_MICROB_PACKAGE            , USB_MICROB     , 0.8764, 0.5550, 90.0
XOSCRF   , TSX-3225            , 16MHz     , 0.6240, 0.7825, 0.0
